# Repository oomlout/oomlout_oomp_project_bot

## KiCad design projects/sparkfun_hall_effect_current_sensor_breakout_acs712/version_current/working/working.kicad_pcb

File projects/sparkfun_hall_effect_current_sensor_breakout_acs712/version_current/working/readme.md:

# Hall-Effect_Current_Sensor_Breakout-ACS712 by sparkfun  
This is a harvested standardized copy of a project from github.  
The original project can be found at:  
https://github.com/sparkfun/Hall-Effect_Current_Sensor_Breakout-ACS712  
Please consult that link for additional, details, files, and license information.  
Note: It was auto harvested and if the original repo had more than one board file or anything out of the ordinary the files here are likely not representative.

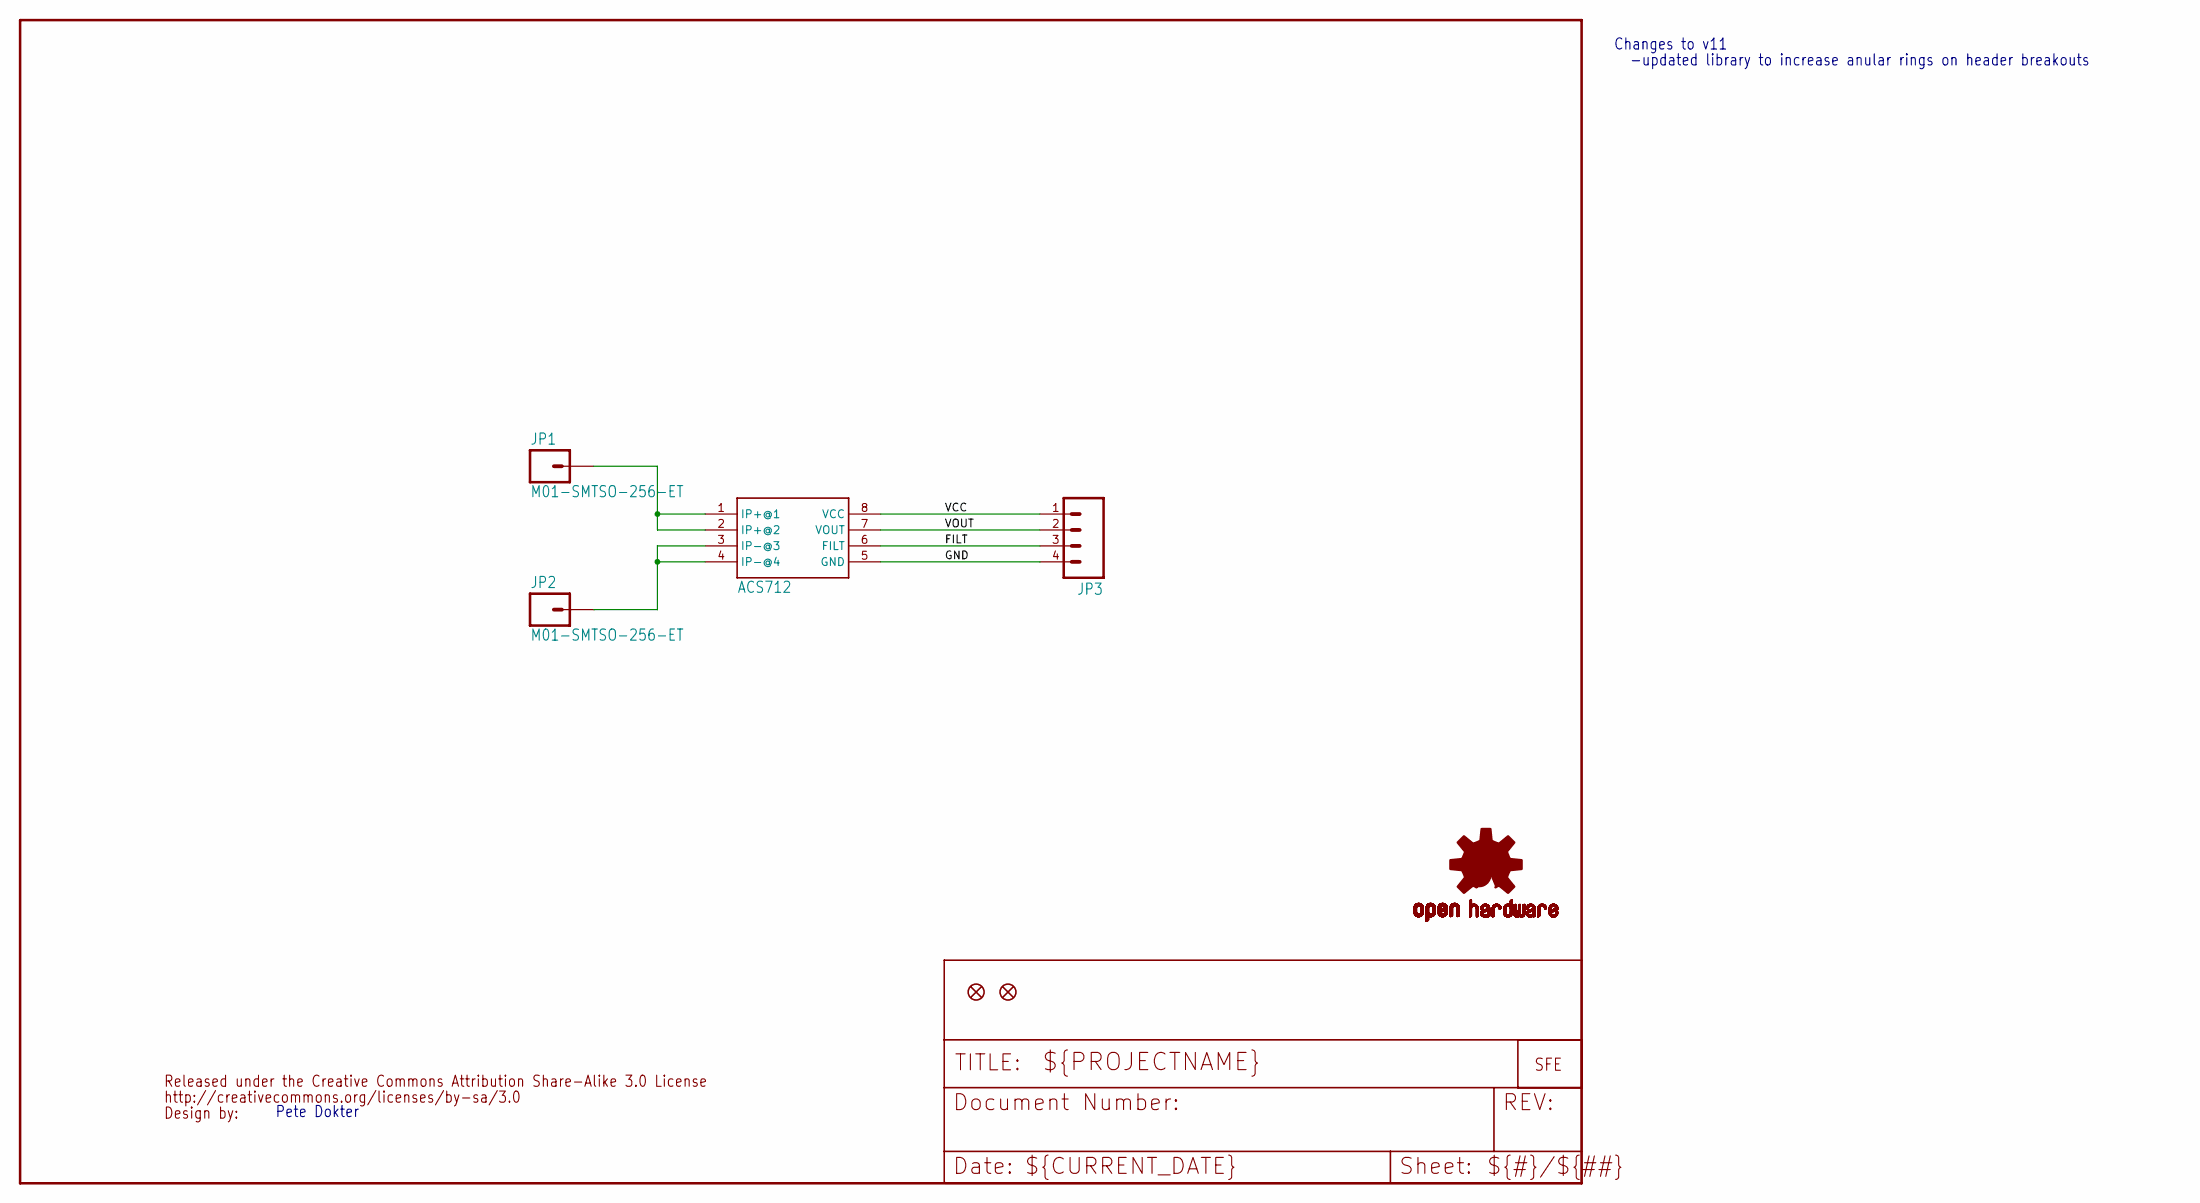
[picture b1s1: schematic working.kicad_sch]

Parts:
JP1, JP2: M01-SMTSO-256-ET; SMTSO-256-ET
JP3: M04PTH; 1X04
JP4, JP5: FIDUCIALUFIDUCIAL; MICRO-FIDUCIAL
U$1: ACS712; SO08
U$2: LOGO-FLAME-LARGE
U$3: OSHW-LOGOS; OSHW-LOGO-S
U$4: CREATIVE_COMMONS

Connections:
FILT: JP3.3, U$1.6 (FILT)
GND: JP3.4, U$1.5 (GND)
unnamed: JP1.P$1, U$1.1 (IP+@1), U$1.2 (IP+@2)
unnamed: JP2.P$1, U$1.3 (IP-@3), U$1.4 (IP-@4)
VCC: JP3.1, U$1.8 (VCC)
VOUT: JP3.2, U$1.7 (VOUT)

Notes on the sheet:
-updated library to increase anular rings on header breakouts
Changes to v11
Pete Dokter

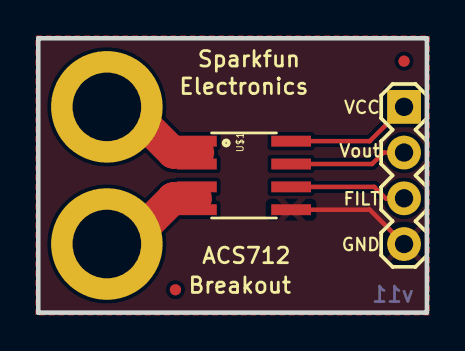
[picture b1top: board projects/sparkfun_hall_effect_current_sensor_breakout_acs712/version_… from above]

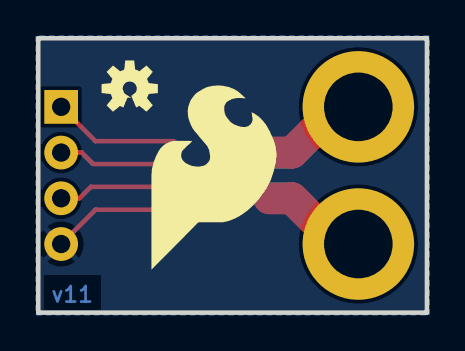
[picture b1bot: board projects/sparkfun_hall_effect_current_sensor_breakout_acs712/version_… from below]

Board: 16 copper layers, 21.6 x 15.2 mm, 9 parts (2 on the bottom side), 6 nets.

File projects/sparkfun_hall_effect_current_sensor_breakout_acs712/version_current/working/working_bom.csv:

Row,Description,Part,References,Value,Footprint,Quantity Per PCB,Status,Datasheet
1,,M01-SMTSO-256-ET,JP1 JP2,M01-SMTSO-256-ET,SMTSO-256-ET,2, ,
2,,M04PTH,JP3,M04PTH,1X04,1, ,
3,,ACS712,U$1,ACS712,SO08,1, ,
4,,CREATIVE_COMMONS,U$4,CREATIVE_COMMONS,CREATIVE_COMMONS,1, ,
5,,LOGO-FLAME-LARGE,U$2,LOGO-FLAME-LARGE,LOGO-FLAME-LARGE,1, ,
6,,OSHW-LOGOS,U$3,OSHW-LOGOS,OSHW-LOGO-S,1, ,





Project info:
Schematic:,working
Variant:,default
Revision:,
Date:,2023-08-06_12-56-03
KiCad Version:,7.0.6-7.0.6~ubuntu22.04.1
Statistics:
Component Groups:,6
Component Count:,7 (0 SMD/ 0 THT)
Fitted Components:,7 (0 SMD/ 0 THT)
Number of PCBs:,1
Total Components:,7

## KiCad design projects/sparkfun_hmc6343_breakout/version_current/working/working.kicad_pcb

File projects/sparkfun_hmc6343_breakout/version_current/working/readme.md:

# HMC6343_Breakout by sparkfun  
This is a harvested standardized copy of a project from github.  
The original project can be found at:  
https://github.com/sparkfun/HMC6343_Breakout  
Please consult that link for additional, details, files, and license information.  
Note: It was auto harvested and if the original repo had more than one board file or anything out of the ordinary the files here are likely not representative.

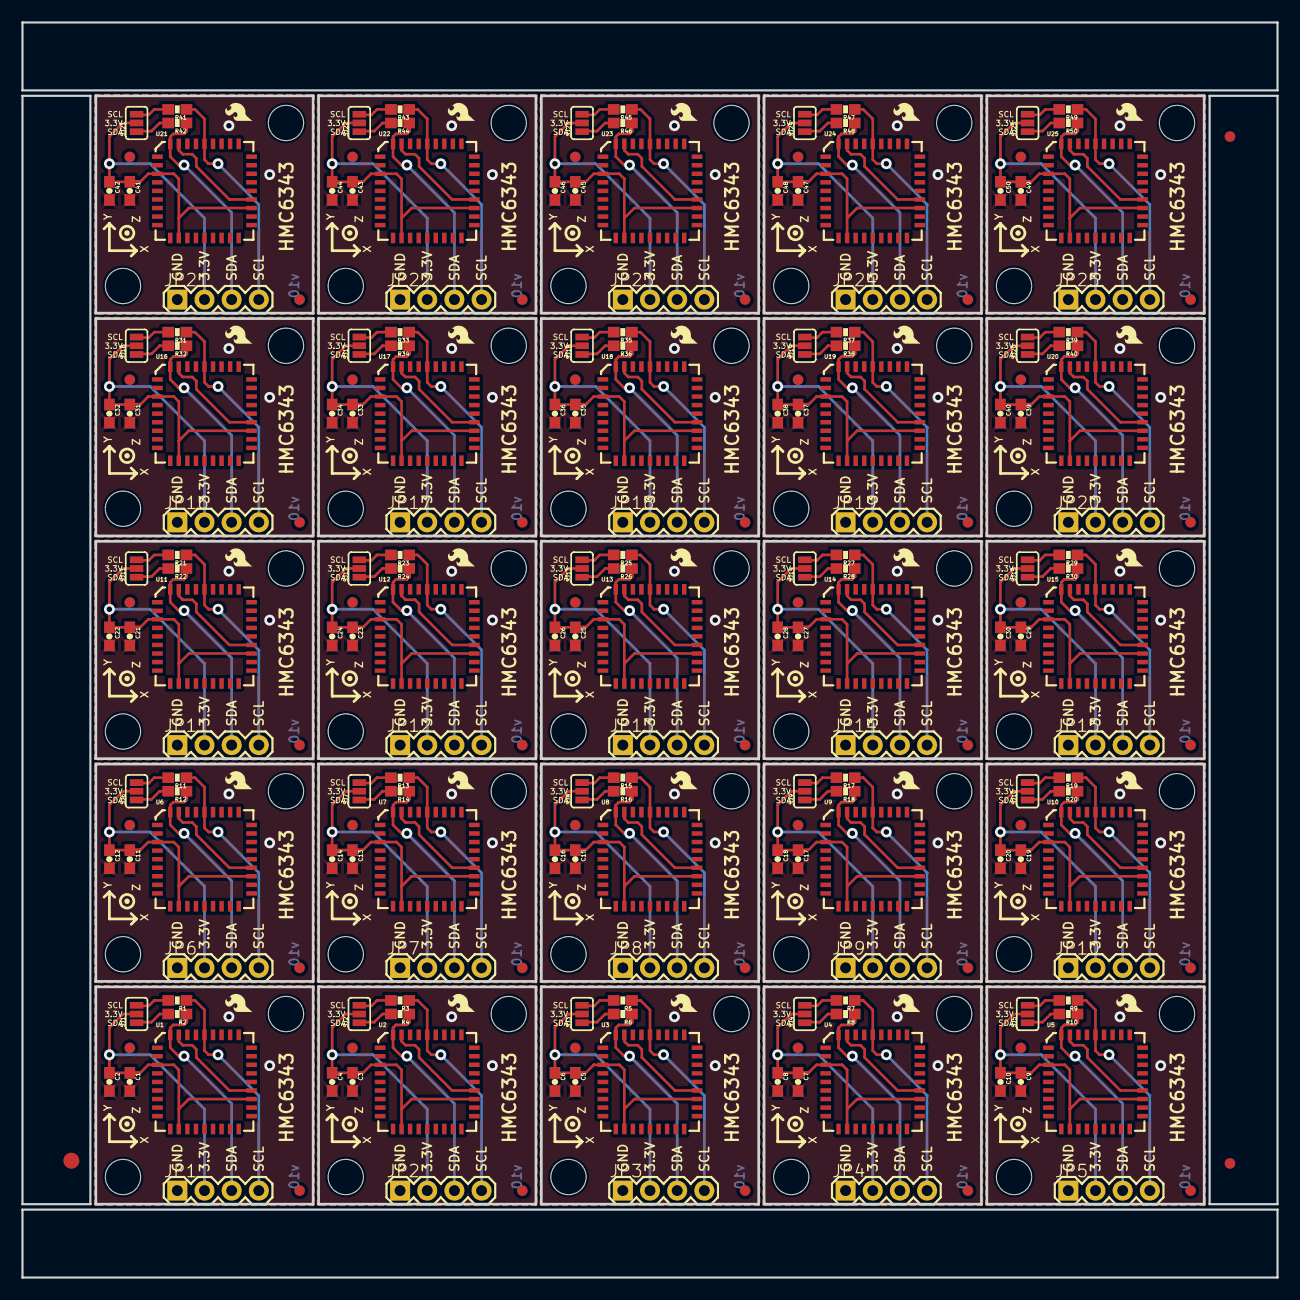
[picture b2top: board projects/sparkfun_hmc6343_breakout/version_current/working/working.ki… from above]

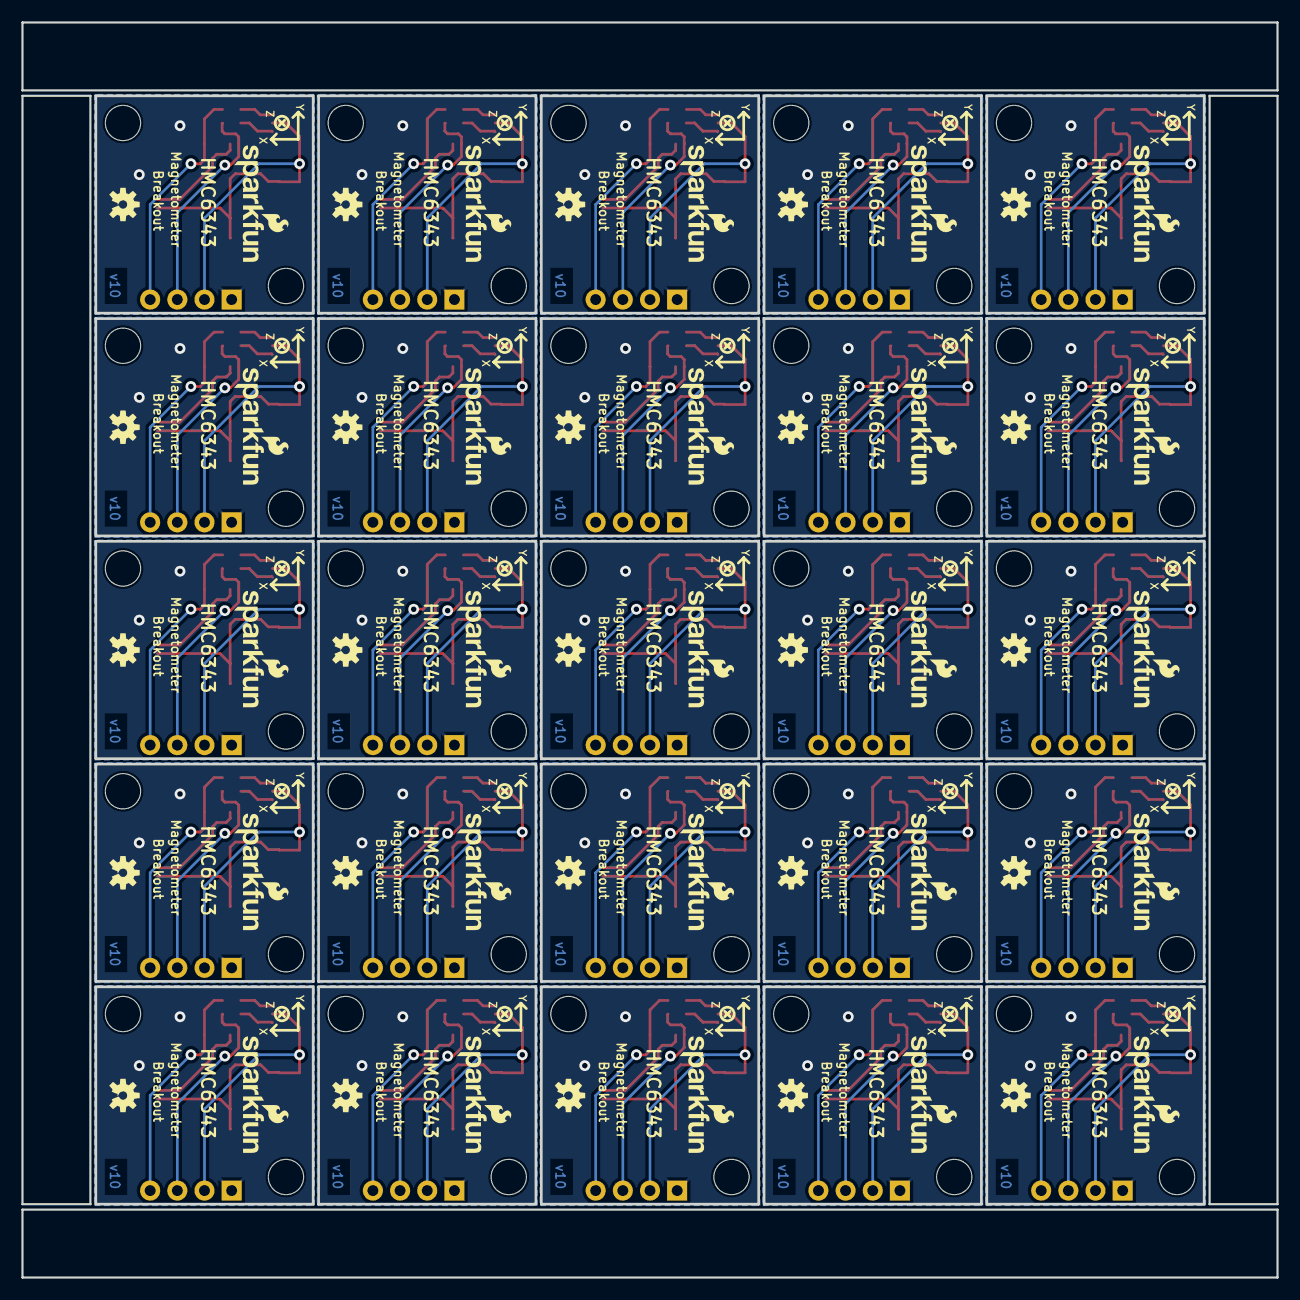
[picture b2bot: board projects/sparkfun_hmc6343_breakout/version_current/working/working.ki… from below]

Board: 2 copper layers, 117.3 x 117.3 mm, 353 parts (50 on the bottom side), 175 nets.

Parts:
C1, C3, C5, C7, C9, C11, C13, C15, C17, C19, C21, C23, C25, C27, C29, C31, C33, C35, C37, C39, C41, C43, C45, C47, C49: 0.1uF; 0603-CAP
C2, C4, C6, C8, C10, C12, C14, C16, C18, C20, C22, C24, C26, C28, C30, C32, C34, C36, C38, C40, C42, C44, C46, C48, C50: 1.0uF; 0603-CAP
E$1: FIDUCIAL-1.5X3
E$4, E$6: FIDUCIAL-1X2
FID1, FID2, FID3, FID4, FID5, FID6, FID7, FID8, FID9, FID10, FID11, FID12, FID13, FID14, FID15, FID16, FID17, FID18, FID19, FID20, FID21, FID22, FID23, FID24, FID25, FID26, FID27, FID28, FID29, FID30, FID31, FID32, FID33, FID34, FID35, FID36, FID37, FID38, FID39, FID40, FID41, FID42, FID43, FID44, FID45, FID46, FID47, FID48, FID49, FID50: FIDUCIAL1X2; FIDUCIAL-1X2
JP1, JP2, JP3, JP4, JP5, JP6, JP7, JP8, JP9, JP10, JP11, JP12, JP13, JP14, JP15, JP16, JP17, JP18, JP19, JP20, JP21, JP22, JP23, JP24, JP25: 1X04
LOGO1, LOGO4, LOGO7, LOGO10, LOGO13, LOGO16, LOGO19, LOGO22, LOGO25, LOGO28, LOGO31, LOGO34, LOGO37, LOGO40, LOGO43, LOGO46, LOGO49, LOGO52, LOGO55, LOGO58, LOGO61, LOGO64, LOGO67, LOGO70, LOGO73: SFE_LOGO_FLAME.1_INCH; SFE_LOGO_FLAME_.1
LOGO2, LOGO5, LOGO8, LOGO11, LOGO14, LOGO17, LOGO20, LOGO23, LOGO26, LOGO29, LOGO32, LOGO35, LOGO38, LOGO41, LOGO44, LOGO47, LOGO50, LOGO53, LOGO56, LOGO59, LOGO62, LOGO65, LOGO68, LOGO71, LOGO74: SFE_LOGO_NAME_FLAME.1_INCH; SFE_LOGO_NAME_FLAME_.1
LOGO3, LOGO6, LOGO9, LOGO12, LOGO15, LOGO18, LOGO21, LOGO24, LOGO27, LOGO30, LOGO33, LOGO36, LOGO39, LOGO42, LOGO45, LOGO48, LOGO51, LOGO54, LOGO57, LOGO60, LOGO63, LOGO66, LOGO69, LOGO72, LOGO75: OSHW-LOGOS; OSHW-LOGO-S
R1, R2, R3, R4, R5, R6, R7, R8, R9, R10, R11, R12, R13, R14, R15, R16, R17, R18, R19, R20, R21, R22, R23, R24, R25, R26, R27, R28, R29, R30, R31, R32, R33, R34, R35, R36, R37, R38, R39, R40, R41, R42, R43, R44, R45, R46, R47, R48, R49, R50: 10K; 0603-RES
SJ1, SJ2, SJ3, SJ4, SJ5, SJ6, SJ7, SJ8, SJ9, SJ10, SJ11, SJ12, SJ13, SJ14, SJ15, SJ16, SJ17, SJ18, SJ19, SJ20, SJ21, SJ22, SJ23, SJ24, SJ25: SJ_3_PASTE1&2&3
STANDOFF1, STANDOFF2, STANDOFF3, STANDOFF4, STANDOFF5, STANDOFF6, STANDOFF7, STANDOFF8, STANDOFF9, STANDOFF10, STANDOFF11, STANDOFF12, STANDOFF13, STANDOFF14, STANDOFF15, STANDOFF16, STANDOFF17, STANDOFF18, STANDOFF19, STANDOFF20, STANDOFF21, STANDOFF22, STANDOFF23, STANDOFF24, STANDOFF25, STANDOFF26, STANDOFF27, STANDOFF28, STANDOFF29, STANDOFF30, STANDOFF31, STANDOFF32, STANDOFF33, STANDOFF34, STANDOFF35, STANDOFF36, STANDOFF37, STANDOFF38, STANDOFF39, STANDOFF40, STANDOFF41, STANDOFF42, STANDOFF43, STANDOFF44, STANDOFF45, STANDOFF46, STANDOFF47, STANDOFF48, STANDOFF49, STANDOFF50: STAND-OFF
U1, U2, U3, U4, U5, U6, U7, U8, U9, U10, U11, U12, U13, U14, U15, U16, U17, U18, U19, U20, U21, U22, U23, U24, U25: HMC6343A; LCC36

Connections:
3.3V: C1.1, C2.1, JP1.2, SJ1.2, U1.3, U1.11, U1.21
3.3V1: C3.1, C4.1, JP2.2, SJ2.2, U2.3, U2.11, U2.21
3.3V2: C5.1, C6.1, JP3.2, SJ3.2, U3.3, U3.11, U3.21
3.3V3: C7.1, C8.1, JP4.2, SJ4.2, U4.3, U4.11, U4.21
3.3V4: C9.1, C10.1, JP5.2, SJ5.2, U5.3, U5.11, U5.21
3.3V5: C11.1, C12.1, JP6.2, SJ6.2, U6.3, U6.11, U6.21
3.3V6: C13.1, C14.1, JP7.2, SJ7.2, U7.3, U7.11, U7.21
3.3V7: C15.1, C16.1, JP8.2, SJ8.2, U8.3, U8.11, U8.21
3.3V8: C17.1, C18.1, JP9.2, SJ9.2, U9.3, U9.11, U9.21
3.3V9: C19.1, C20.1, JP10.2, SJ10.2, U10.3, U10.11, U10.21
3.3V10: C21.1, C22.1, JP11.2, SJ11.2, U11.3, U11.11, U11.21
3.3V11: C23.1, C24.1, JP12.2, SJ12.2, U12.3, U12.11, U12.21
3.3V12: C25.1, C26.1, JP13.2, SJ13.2, U13.3, U13.11, U13.21
3.3V13: C27.1, C28.1, JP14.2, SJ14.2, U14.3, U14.11, U14.21
3.3V14: C29.1, C30.1, JP15.2, SJ15.2, U15.3, U15.11, U15.21
3.3V15: C31.1, C32.1, JP16.2, SJ16.2, U16.3, U16.11, U16.21
3.3V16: C33.1, C34.1, JP17.2, SJ17.2, U17.3, U17.11, U17.21
3.3V17: C35.1, C36.1, JP18.2, SJ18.2, U18.3, U18.11, U18.21
3.3V18: C37.1, C38.1, JP19.2, SJ19.2, U19.3, U19.11, U19.21
3.3V19: C39.1, C40.1, JP20.2, SJ20.2, U20.3, U20.11, U20.21
3.3V20: C41.1, C42.1, JP21.2, SJ21.2, U21.3, U21.11, U21.21
3.3V21: C43.1, C44.1, JP22.2, SJ22.2, U22.3, U22.11, U22.21
3.3V22: C45.1, C46.1, JP23.2, SJ23.2, U23.3, U23.11, U23.21
3.3V23: C47.1, C48.1, JP24.2, SJ24.2, U24.3, U24.11, U24.21
3.3V24: C49.1, C50.1, JP25.2, SJ25.2, U25.3, U25.11, U25.21
GND: C1.2, C2.2, JP1.1, U1.25, U1.29
GND1: C3.2, C4.2, JP2.1, U2.25, U2.29
GND2: C5.2, C6.2, JP3.1, U3.25, U3.29
GND3: C7.2, C8.2, JP4.1, U4.25, U4.29
GND4: C9.2, C10.2, JP5.1, U5.25, U5.29
GND5: C11.2, C12.2, JP6.1, U6.25, U6.29
GND6: C13.2, C14.2, JP7.1, U7.25, U7.29
GND7: C15.2, C16.2, JP8.1, U8.25, U8.29
GND8: C17.2, C18.2, JP9.1, U9.25, U9.29
GND9: C19.2, C20.2, JP10.1, U10.25, U10.29
GND10: C21.2, C22.2, JP11.1, U11.25, U11.29
GND11: C23.2, C24.2, JP12.1, U12.25, U12.29
GND12: C25.2, C26.2, JP13.1, U13.25, U13.29
GND13: C27.2, C28.2, JP14.1, U14.25, U14.29
GND14: C29.2, C30.2, JP15.1, U15.25, U15.29
GND15: C31.2, C32.2, JP16.1, U16.25, U16.29
GND16: C33.2, C34.2, JP17.1, U17.25, U17.29
GND17: C35.2, C36.2, JP18.1, U18.25, U18.29
GND18: C37.2, C38.2, JP19.1, U19.25, U19.29
GND19: C39.2, C40.2, JP20.1, U20.25, U20.29
GND20: C41.2, C42.2, JP21.1, U21.25, U21.29
GND21: C43.2, C44.2, JP22.1, U22.25, U22.29
GND22: C45.2, C46.2, JP23.1, U23.25, U23.29
GND23: C47.2, C48.2, JP24.1, U24.25, U24.29
GND24: C49.2, C50.2, JP25.1, U25.25, U25.29
unnamed: U1.22, U1.35
unnamed: U2.22, U2.35
unnamed: R3.2, SJ2.3
unnamed: R1.2, SJ1.3
unnamed: R2.2, SJ1.1
unnamed: R4.2, SJ2.1
unnamed: U3.22, U3.35
unnamed: R5.2, SJ3.3
unnamed: R6.2, SJ3.1
unnamed: U4.22, U4.35
unnamed: R7.2, SJ4.3
unnamed: R8.2, SJ4.1
unnamed: U5.22, U5.35
unnamed: R9.2, SJ5.3
unnamed: R10.2, SJ5.1
unnamed: U6.22, U6.35
unnamed: R11.2, SJ6.3
unnamed: R12.2, SJ6.1
unnamed: U7.22, U7.35
unnamed: R13.2, SJ7.3
unnamed: R14.2, SJ7.1
unnamed: U8.22, U8.35
unnamed: R15.2, SJ8.3
unnamed: R16.2, SJ8.1
unnamed: U9.22, U9.35
unnamed: R17.2, SJ9.3
unnamed: R18.2, SJ9.1
unnamed: U10.22, U10.35
unnamed: R19.2, SJ10.3
unnamed: R20.2, SJ10.1
unnamed: U11.22, U11.35
unnamed: R21.2, SJ11.3
unnamed: R22.2, SJ11.1
unnamed: U12.22, U12.35
unnamed: R23.2, SJ12.3
unnamed: R24.2, SJ12.1
unnamed: U13.22, U13.35
unnamed: R25.2, SJ13.3
unnamed: R26.2, SJ13.1
unnamed: U14.22, U14.35
unnamed: R27.2, SJ14.3
unnamed: R28.2, SJ14.1
unnamed: U15.22, U15.35
unnamed: R29.2, SJ15.3
unnamed: R30.2, SJ15.1
unnamed: U16.22, U16.35
unnamed: R31.2, SJ16.3
unnamed: R32.2, SJ16.1
unnamed: U17.22, U17.35
unnamed: R33.2, SJ17.3
unnamed: R34.2, SJ17.1
unnamed: U18.22, U18.35
unnamed: R35.2, SJ18.3
unnamed: R36.2, SJ18.1
unnamed: U19.22, U19.35
unnamed: R37.2, SJ19.3
unnamed: R38.2, SJ19.1
unnamed: U20.22, U20.35
unnamed: R39.2, SJ20.3
unnamed: R40.2, SJ20.1
unnamed: U21.22, U21.35
unnamed: R41.2, SJ21.3
unnamed: R42.2, SJ21.1
unnamed: U22.22, U22.35
unnamed: R43.2, SJ22.3
unnamed: R44.2, SJ22.1
unnamed: U23.22, U23.35
unnamed: R45.2, SJ23.3
unnamed: R46.2, SJ23.1
unnamed: U24.22, U24.35
unnamed: R47.2, SJ24.3
unnamed: R48.2, SJ24.1
unnamed: U25.22, U25.35
unnamed: R49.2, SJ25.3
unnamed: R50.2, SJ25.1
SCL: JP1.4, R1.1, U1.32
SCL1: JP2.4, R3.1, U2.32
SCL2: JP3.4, R5.1, U3.32
SCL3: JP4.4, R7.1, U4.32
SCL4: JP5.4, R9.1, U5.32
SCL5: JP6.4, R11.1, U6.32
SCL6: JP7.4, R13.1, U7.32
SCL7: JP8.4, R15.1, U8.32
SCL8: JP9.4, R17.1, U9.32
SCL9: JP10.4, R19.1, U10.32
SCL10: JP11.4, R21.1, U11.32
SCL11: JP12.4, R23.1, U12.32
SCL12: JP13.4, R25.1, U13.32
SCL13: JP14.4, R27.1, U14.32
SCL14: JP15.4, R29.1, U15.32
SCL15: JP16.4, R31.1, U16.32
SCL16: JP17.4, R33.1, U17.32
SCL17: JP18.4, R35.1, U18.32
SCL18: JP19.4, R37.1, U19.32
SCL19: JP20.4, R39.1, U20.32
SCL20: JP21.4, R41.1, U21.32
SCL21: JP22.4, R43.1, U22.32
SCL22: JP23.4, R45.1, U23.32
SCL23: JP24.4, R47.1, U24.32
SCL24: JP25.4, R49.1, U25.32
SDA: JP1.3, R2.1, U1.36
SDA1: JP2.3, R4.1, U2.36
SDA2: JP3.3, R6.1, U3.36
SDA3: JP4.3, R8.1, U4.36
SDA4: JP5.3, R10.1, U5.36
SDA5: JP6.3, R12.1, U6.36
SDA6: JP7.3, R14.1, U7.36
SDA7: JP8.3, R16.1, U8.36
SDA8: JP9.3, R18.1, U9.36
SDA9: JP10.3, R20.1, U10.36
SDA10: JP11.3, R22.1, U11.36
SDA11: JP12.3, R24.1, U12.36
SDA12: JP13.3, R26.1, U13.36
SDA13: JP14.3, R28.1, U14.36
SDA14: JP15.3, R30.1, U15.36
SDA15: JP16.3, R32.1, U16.36
SDA16: JP17.3, R34.1, U17.36
SDA17: JP18.3, R36.1, U18.36
SDA18: JP19.3, R38.1, U19.36
SDA19: JP20.3, R40.1, U20.36
SDA20: JP21.3, R42.1, U21.36
SDA21: JP22.3, R44.1, U22.36
SDA22: JP23.3, R46.1, U23.36
SDA23: JP24.3, R48.1, U24.36
SDA24: JP25.3, R50.1, U25.36

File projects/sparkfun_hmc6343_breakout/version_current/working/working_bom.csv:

Row,Description,Part,References,Value,Footprint,Quantity Per PCB,Status,Datasheet
1,,0.1UF-25V(+80/-20%)(0603),C1,0.1uF,0603-CAP,1, ,
2,,1.0UF-16V-10%(0603),C2,1.0uF,0603-CAP,1, ,
3,,FRAME-LETTER,FRAME1,FRAME-LETTER,CREATIVE_COMMONS,1, ,
4,,M04PTH,JP1,M04PTH,1X04,1, ,
5,,OSHW-LOGOS,LOGO3,OSHW-LOGOS,OSHW-LOGO-S,1, ,
6,,SFE_LOGO_FLAME.1_INCH,LOGO1,SFE_LOGO_FLAME.1_INCH,SFE_LOGO_FLAME_.1,1, ,
7,,SFE_LOGO_NAME_FLAME.1_INCH,LOGO2,SFE_LOGO_NAME_FLAME.1_INCH,SFE_LOGO_NAME_FLAME_.1,1, ,
8,,10KOHM1/10W1%(0603)0603,R1 R2,10K,0603-RES,2, ,
9,,STAND-OFF,STANDOFF1 STANDOFF2,STAND-OFF,STAND-OFF,2, ,
10,,HMC6343A,U1,HMC6343A,LCC36,1, ,





Project info:
Schematic:,working
Variant:,default
Revision:,
Date:,2023-08-06_12-56-03
KiCad Version:,7.0.6-7.0.6~ubuntu22.04.1
Statistics:
Component Groups:,10
Component Count:,12 (0 SMD/ 0 THT)
Fitted Components:,12 (0 SMD/ 0 THT)
Number of PCBs:,1
Total Components:,12

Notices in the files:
projects/sparkfun_hall_effect_current_sensor_breakout_acs712/version_current/working/working.kicad_sch:
http://creativecommons.org/licenses/by-sa/3.0
Released under the Creative Commons Attribution Share-Alike 3.0 License
